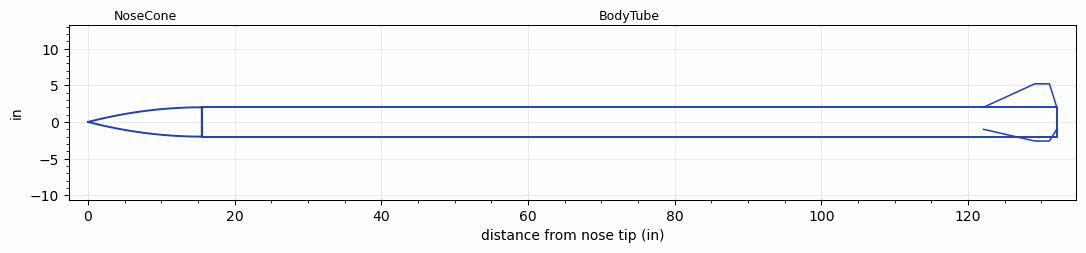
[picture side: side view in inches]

<RASAeroDocument>
 <FileVersion>2</FileVersion>
 <RocketDesign>
  <NoseCone>
   <Length>15.516</Length>
   <Diameter>4</Diameter>
   <Shape>Parabolic</Shape>
   <BluntRadius>0.1</BluntRadius>
   <Location>0</Location>
  </NoseCone>
  <BodyTube>
   <Length>116.6</Length>
   <Diameter>4</Diameter>
   <LaunchShoeArea>0.09</LaunchShoeArea>
   <Location>15.516</Location>
   <Fin>
    <Count>3</Count>
    <Chord>10</Chord>
    <Span>3.2</Span>
    <SweepDistance>7</SweepDistance>
    <TipChord>2</TipChord>
    <Thickness>0.25</Thickness>
    <LERadius>0.125</LERadius>
    <Location>10</Location>
    <AirfoilSection>Double Wedge</AirfoilSection>
    <FX1>1</FX1>
   </Fin>
  </BodyTube>
  <Surface>Rough Camouflage Paint</Surface>
  <ModifiedBarrowman>True</ModifiedBarrowman>
  <Turbulence>False</Turbulence>
  <UseBooster1>False</UseBooster1>
  <UseBooster2>False</UseBooster2>
 </RocketDesign>
 <LaunchSite>
  <Altitude>4596</Altitude>
  <Pressure>0</Pressure>
  <RodAngle>5</RodAngle>
  <RodLength>18</RodLength>
  <Temperature>70</Temperature>
  <WindSpeed>44</WindSpeed>
 </LaunchSite>
 <Recovery>
  <Altitude1>1000</Altitude1>
  <Altitude2>1500</Altitude2>
  <DeviceType1>Parachute</DeviceType1>
  <DeviceType2>Parachute</DeviceType2>
  <Event1>True</Event1>
  <Event2>True</Event2>
  <Size1>30.57</Size1>
  <Size2>96</Size2>
  <EventType1>Apogee</EventType1>
  <EventType2>Altitude</EventType2>
  <CD1>0.75</CD1>
  <CD2>2.2</CD2>
 </Recovery>
 <SimulationList>
  <Simulation>
   <SustainerEngine>N2900-CL  (CTI)</SustainerEngine>
   <SustainerLaunchWt>62.8</SustainerLaunchWt>
   <SustainerNozzleDiameter>2</SustainerNozzleDiameter>
   <SustainerCG>73.8</SustainerCG>
   <SustainerIgnitionDelay>0</SustainerIgnitionDelay>
   <Booster1SeparationDelay>0</Booster1SeparationDelay>
   <Booster1IgnitionDelay>0</Booster1IgnitionDelay>
   <IncludeBooster1>False</IncludeBooster1>
   <Booster2Delay>0</Booster2Delay>
   <IncludeBooster2>False</IncludeBooster2>
   <TimetoApogee>42.44888</TimetoApogee>
   <MaxAltitude>32677.65</MaxAltitude>
   <MaxVelocity>1995.501</MaxVelocity>
  </Simulation>
  <Simulation>
   <SustainerEngine>N2900-CL  (CTI)</SustainerEngine>
   <SustainerLaunchWt>67.8</SustainerLaunchWt>
   <SustainerNozzleDiameter>2</SustainerNozzleDiameter>
   <SustainerCG>74.2</SustainerCG>
   <SustainerIgnitionDelay>0</SustainerIgnitionDelay>
   <Booster1SeparationDelay>0</Booster1SeparationDelay>
   <Booster1IgnitionDelay>0</Booster1IgnitionDelay>
   <IncludeBooster1>False</IncludeBooster1>
   <Booster2Delay>0</Booster2Delay>
   <IncludeBooster2>False</IncludeBooster2>
   <TimetoApogee>44.54853</TimetoApogee>
   <MaxAltitude>34035.13</MaxAltitude>
   <MaxVelocity>1836.225</MaxVelocity>
  </Simulation>
  <Simulation>
   <SustainerEngine>N2900-CL  (CTI)</SustainerEngine>
   <SustainerLaunchWt>72.8</SustainerLaunchWt>
   <SustainerNozzleDiameter>2</SustainerNozzleDiameter>
   <SustainerCG>74.5</SustainerCG>
   <SustainerIgnitionDelay>0</SustainerIgnitionDelay>
   <Booster1SeparationDelay>0</Booster1SeparationDelay>
   <Booster1IgnitionDelay>0</Booster1IgnitionDelay>
   <IncludeBooster1>False</IncludeBooster1>
   <Booster2Delay>0</Booster2Delay>
   <IncludeBooster2>False</IncludeBooster2>
   <TimetoApogee>40.51921</TimetoApogee>
   <MaxAltitude>28032.61</MaxAltitude>
   <MaxVelocity>1701.514</MaxVelocity>
  </Simulation>
  <Simulation>
   <SustainerEngine>N3300  (AT)</SustainerEngine>
   <SustainerLaunchWt>58.1</SustainerLaunchWt>
   <SustainerNozzleDiameter>2</SustainerNozzleDiameter>
   <SustainerCG>72.8</SustainerCG>
   <SustainerIgnitionDelay>0</SustainerIgnitionDelay>
   <Booster1SeparationDelay>0</Booster1SeparationDelay>
   <Booster1IgnitionDelay>0</Booster1IgnitionDelay>
   <IncludeBooster1>False</IncludeBooster1>
   <Booster2Delay>0</Booster2Delay>
   <IncludeBooster2>False</IncludeBooster2>
   <TimetoApogee>38.42956</TimetoApogee>
   <MaxAltitude>25972.21</MaxAltitude>
   <MaxVelocity>1727.265</MaxVelocity>
  </Simulation>
  <Simulation>
   <SustainerEngine>N2900-CL  (CTI)</SustainerEngine>
   <SustainerLaunchWt>77.8</SustainerLaunchWt>
   <SustainerNozzleDiameter>2</SustainerNozzleDiameter>
   <SustainerCG>74.8</SustainerCG>
   <SustainerIgnitionDelay>0</SustainerIgnitionDelay>
   <Booster1SeparationDelay>0</Booster1SeparationDelay>
   <Booster1IgnitionDelay>0</Booster1IgnitionDelay>
   <IncludeBooster1>False</IncludeBooster1>
   <Booster2Delay>0</Booster2Delay>
   <IncludeBooster2>False</IncludeBooster2>
   <TimetoApogee>42.10894</TimetoApogee>
   <MaxAltitude>28966.67</MaxAltitude>
   <MaxVelocity>1577.022</MaxVelocity>
  </Simulation>
 </SimulationList>
</RASAeroDocument>
